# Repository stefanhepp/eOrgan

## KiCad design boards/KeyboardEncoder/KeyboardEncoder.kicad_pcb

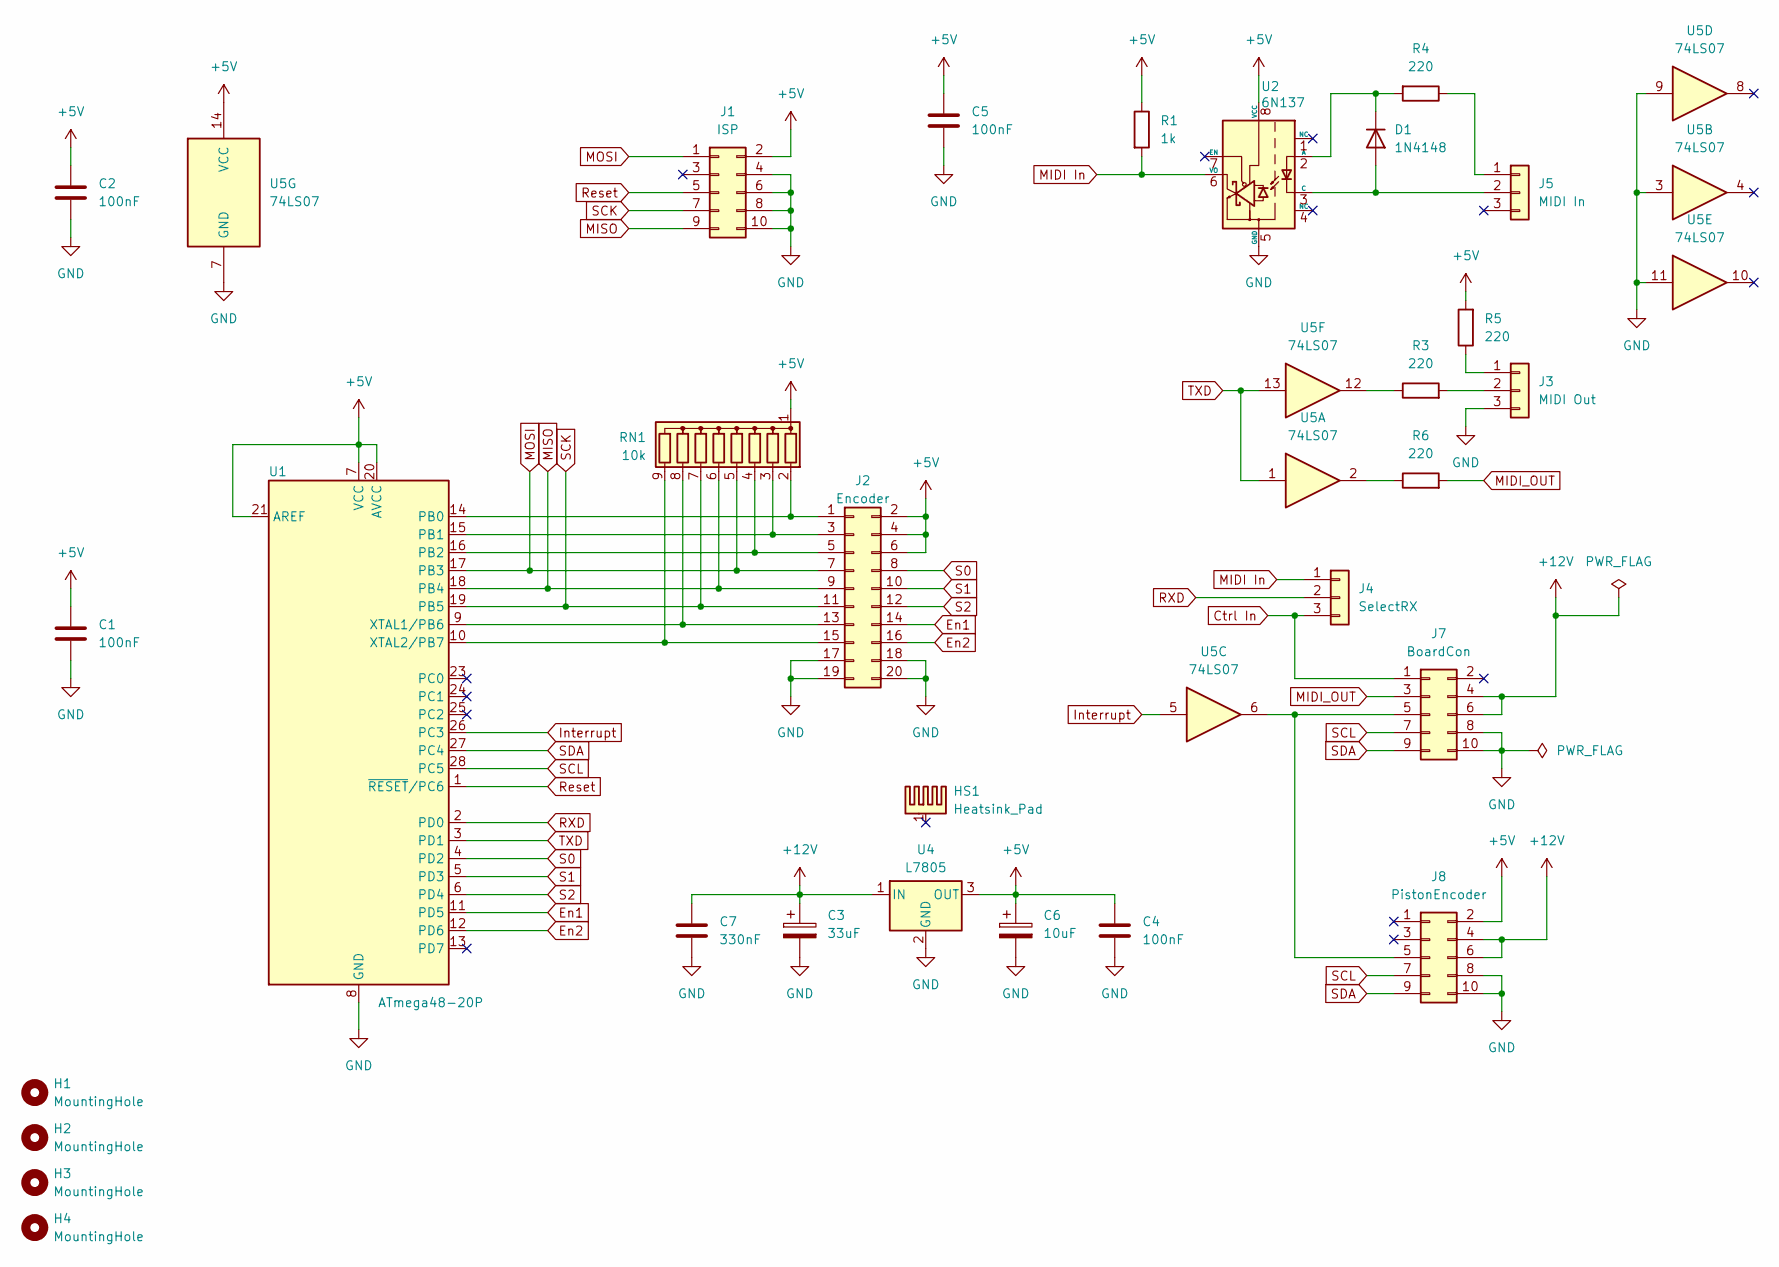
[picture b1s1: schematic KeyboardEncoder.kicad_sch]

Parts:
C1, C2, C4, C5: 100nF; C_Disc_D4.3mm_W1.9mm_P5.00mm
C3: 33uF; CP_Radial_D7.5mm_P2.50mm
C6: 10uF; CP_Radial_D5.0mm_P2.00mm
C7: 330nF; C_Disc_D4.3mm_W1.9mm_P5.00mm
D1: 1N4148; D_DO-35_SOD27_P7.62mm_Horizontal
H1, H2, H3, H4: MountingHole; MountingHole_3.2mm_M3
HS1: Heatsink_Pad; Heatsink_Aavid_TO-220_H12.7mm
J1: ISP; IDC-Header_2x05_P2.54mm_Horizontal
J2: Encoder; IDC-Header_2x10_P2.54mm_Horizontal
J3: MIDI Out; PinHeader_1x03_P2.54mm_Vertical
J4: SelectRX; PinHeader_1x03_P2.54mm_Vertical
J5: MIDI In; PinHeader_1x03_P2.54mm_Vertical
J7: BoardCon; IDC-Header_2x05_P2.54mm_Horizontal
J8: PistonEncoder; IDC-Header_2x05_P2.54mm_Vertical
R1: 1k; R_Axial_DIN0207_L6.3mm_D2.5mm_P2.54mm_Vertical
R3, R4, R5, R6: 220; R_Axial_DIN0207_L6.3mm_D2.5mm_P10.16mm_Horizontal
RN1: 10k; R_Array_SIP9
U1: ATmega48-20P; DIP-28_W7.62mm
U2: 6N137; DIP-8_W7.62mm
U4: L7805; TO-220-3_Vertical
U5: 74LS07; DIP-14_W7.62mm

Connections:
+5V: C1.1, C2.1, C4.1, C5.1, C6.1, J1.2, J2.2, J2.4, J2.6, J8.2, R1.1, R5.2, RN1.1 (common), U1.7 (VCC), U1.20 (AVCC), U1.21 (AREF), U2.8 (VCC), U4.3 (OUT), U5.14 (VCC)
+12V: C3.1, C7.1, J7.4, J7.6, J8.4, J8.6, U4.1 (IN)
Ctrl In: J4.3, J7.1
En1: J2.14, U1.11 (PD5)
En2: J2.16, U1.12 (PD6)
GND: C1.2, C2.2, C3.2, C4.2, C5.2, C6.2, C7.2, J1.4, J1.6, J1.8, J1.10, J2.17, J2.18, J2.19, J2.20, J3.3, J7.8, J7.10, J8.8, J8.10, U1.8 (GND), U1.22 (GND), U2.5 (GND), U4.2 (GND), U5.3, U5.7 (GND), U5.9, U5.11
Interrupt: U1.26 (PC3), U5.5
MIDI In: J4.1, R1.2, U2.6 (VO)
MIDI_OUT: J7.3, R6.2
MISO: J1.9, J2.9, RN1.6 (R5), U1.18 (PB4)
MOSI: J1.1, J2.7, RN1.5 (R4), U1.17 (PB3)
unnamed: D1.2 (A), J5.2, U2.3 (C)
unnamed: D1.1 (K), R4.2, U2.2 (A)
unnamed: J2.1, RN1.2 (R1), U1.14 (PB0)
unnamed: J2.3, RN1.3 (R2), U1.15 (PB1)
unnamed: J2.5, RN1.4 (R3), U1.16 (PB2)
unnamed: J2.13, RN1.8 (R7), U1.9 (XTAL1/PB6)
unnamed: J2.15, RN1.9 (R8), U1.10 (XTAL2/PB7)
unnamed: J3.1, R5.1
unnamed: J3.2, R3.2
unnamed: J5.1, R4.1
unnamed: J7.5, J8.5, U5.6
unnamed: R3.1, U5.12
unnamed: R6.1, U5.2
RXD: J4.2, U1.2 (PD0)
Reset: J1.5, U1.1 (~RESET/PC6)
S0: J2.8, U1.4 (PD2)
S1: J2.10, U1.5 (PD3)
S2: J2.12, U1.6 (PD4)
SCK: J1.7, J2.11, RN1.7 (R6), U1.19 (PB5)
SCL: J7.7, J8.7, U1.28 (PC5)
SDA: J7.9, J8.9, U1.27 (PC4)
TXD: U1.3 (PD1), U5.1, U5.13

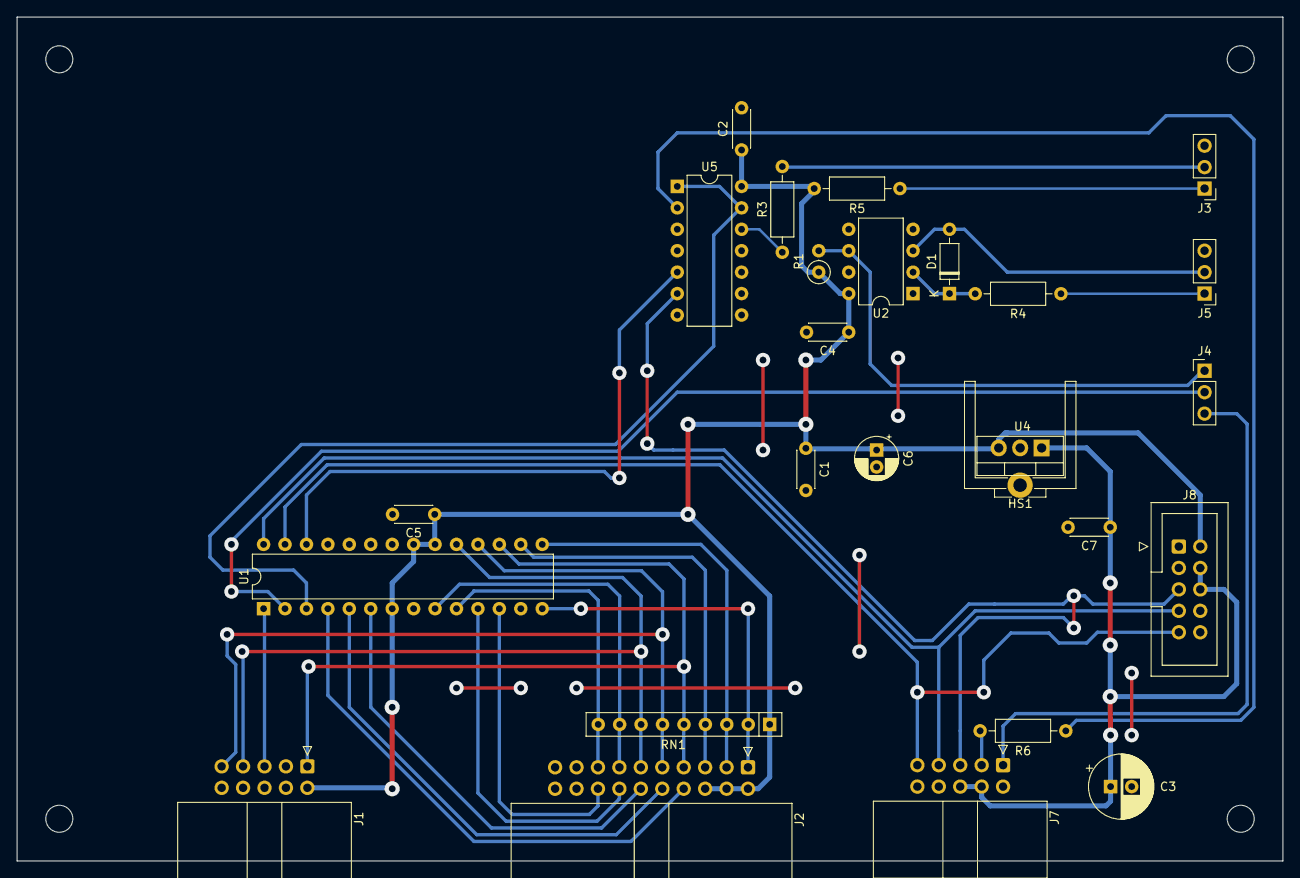
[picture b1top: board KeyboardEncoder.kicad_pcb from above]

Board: 2 copper layers, 150.0 x 100.0 mm, 30 parts (0 on the bottom side), 33 nets.

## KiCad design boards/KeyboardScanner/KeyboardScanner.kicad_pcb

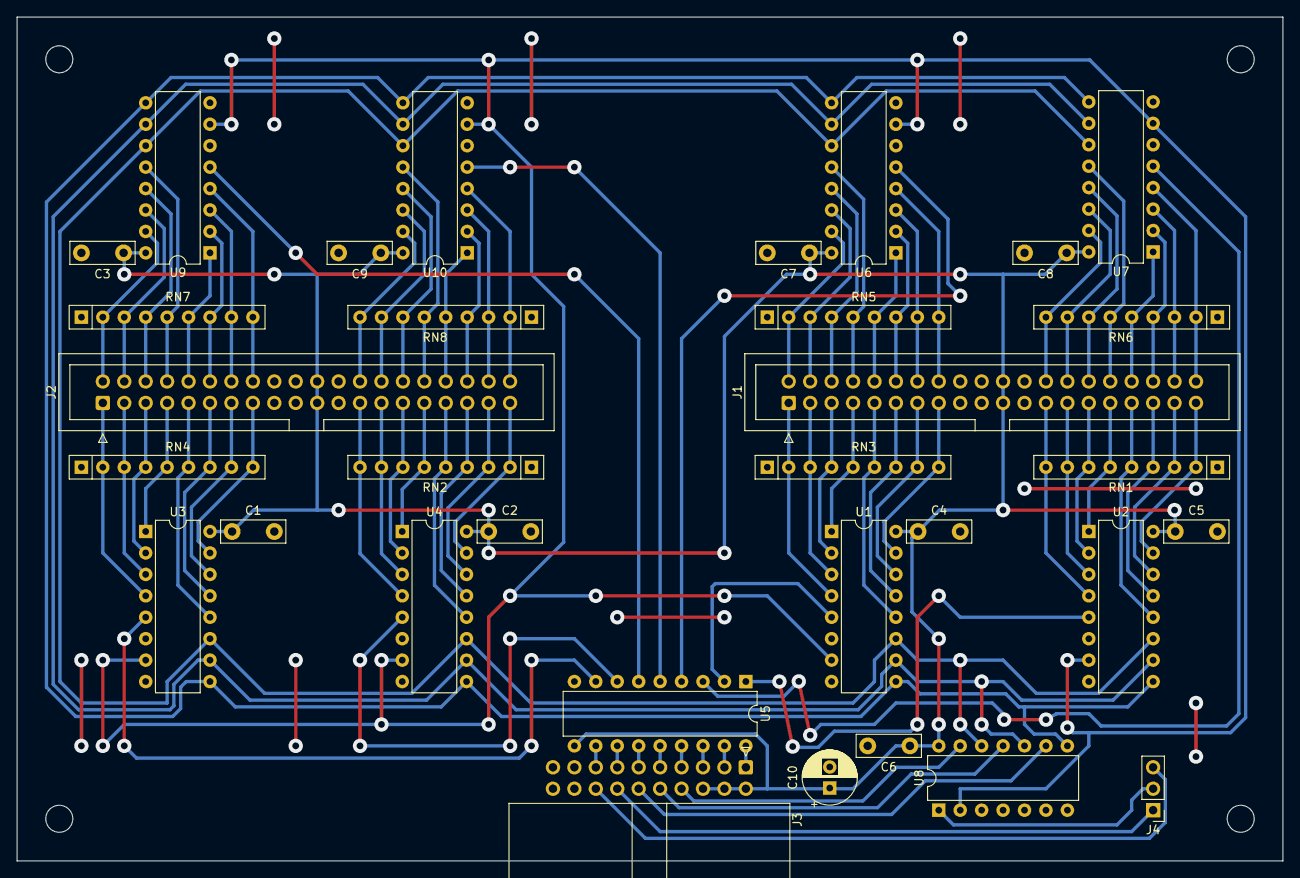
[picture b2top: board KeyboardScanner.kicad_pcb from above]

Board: 2 copper layers, 150.0 x 100.0 mm, 36 parts (0 on the bottom side), 92 nets.

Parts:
C1, C2, C3, C4, C5, C6, C7, C8, C9: 100nF; C_Disc_D7.5mm_W2.5mm_P5.00mm
C10: 47uF; CP_Radial_D6.3mm_P2.50mm
H1, H2, H3, H4: MountingHole; MountingHole_3.2mm_M3
J1, J2: Keyboard1; IDC-Header_2x20_P2.54mm_Vertical
J3: Encoder; IDC-Header_2x10_P2.54mm_Horizontal
J4: Select; PinHeader_1x03_P2.54mm_Vertical
RN1, RN2, RN3, RN4, RN5, RN6, RN7, RN8: 10k; R_Array_SIP9
U1, U2, U3, U4, U6, U7, U9, U10: 74LS151; DIP-16_W7.62mm
U5: ULN2803A; DIP-18_W7.62mm
U8: 4069; DIP-14_W7.62mm

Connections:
+5V: C1.1, C2.1, C3.1, C4.1, C5.1, C6.1, C7.1, C8.1, C9.1, C10.1, J1.21, J1.22, J2.21, J2.22, J3.2, J3.4, J3.6, U1.16 (VCC), U2.16 (VCC), U3.16 (VCC), U4.16 (VCC), U5.10 (COM), U6.16 (VCC), U7.16 (VCC), U8.14 (VDD), U9.16 (VCC), U10.16 (VCC)
En: U1.7 (~E), U2.7 (~E), U3.7 (~E), U4.7 (~E), U6.7 (~E), U7.7 (~E), U8.2, U9.7 (~E), U10.7 (~E)
GND: C1.2, C2.2, C3.2, C4.2, C5.2, C6.2, C7.2, C8.2, C9.2, C10.2, J3.17, J3.18, J3.19, J3.20, RN1.1 (common), RN2.1 (common), RN3.1 (common), RN4.1 (common), RN5.1 (common), RN6.1 (common), RN7.1 (common), RN8.1 (common), U1.8 (GND), U2.8 (GND), U3.8 (GND), U4.8 (GND), U5.9 (GND), U6.8 (GND), U7.8 (GND), U8.3, U8.5, U8.7 (VSS), U9.8 (GND), U10.8 (GND)
K01: J1.1, RN3.2 (R1), U1.4 (I0)
K02: J1.3, RN3.3 (R2), U1.3 (I1)
K03: J1.5, RN3.4 (R3), U1.2 (I2)
K04: J1.7, RN3.5 (R4), U1.1 (I3)
K05: J1.9, RN3.6 (R5), U1.12 (I7)
K06: J1.11, RN3.7 (R6), U1.13 (I6)
K07: J1.13, RN3.8 (R7), U1.14 (I5)
K08: J1.15, RN3.9 (R8), U1.15 (I4)
K09: J1.25, RN1.9 (R8), U2.4 (I0)
K10: J1.27, RN1.8 (R7), U2.3 (I1)
K11: J1.29, RN1.7 (R6), U2.2 (I2)
K12: J1.31, RN1.6 (R5), U2.1 (I3)
K13: J1.33, RN1.5 (R4), U2.12 (I7)
K14: J1.35, RN1.4 (R3), U2.13 (I6)
K15: J1.37, RN1.3 (R2), U2.14 (I5)
K16: J1.39, RN1.2 (R1), U2.15 (I4)
K17: J2.1, RN4.2 (R1), U3.4 (I0)
K18: J2.3, RN4.3 (R2), U3.3 (I1)
K19: J2.5, RN4.4 (R3), U3.2 (I2)
K20: J2.7, RN4.5 (R4), U3.1 (I3)
K21: J2.9, RN4.6 (R5), U3.12 (I7)
K22: J2.11, RN4.7 (R6), U3.13 (I6)
K23: J2.13, RN4.8 (R7), U3.14 (I5)
K24: J2.15, RN4.9 (R8), U3.15 (I4)
K25: J2.25, RN2.9 (R8), U4.4 (I0)
K26: J2.27, RN2.8 (R7), U4.3 (I1)
K27: J2.29, RN2.7 (R6), U4.2 (I2)
K28: J2.31, RN2.6 (R5), U4.1 (I3)
K29: J2.33, RN2.5 (R4), U4.12 (I7)
K30: J2.35, RN2.4 (R3), U4.13 (I6)
K31: J2.37, RN2.3 (R2), U4.14 (I5)
K32: J2.39, RN2.2 (R1), U4.15 (I4)
K33: J1.2, RN5.2 (R1), U6.15 (I4)
K34: J1.4, RN5.3 (R2), U6.14 (I5)
K35: J1.6, RN5.4 (R3), U6.13 (I6)
K36: J1.8, RN5.5 (R4), U6.12 (I7)
K37: J1.10, RN5.6 (R5), U6.1 (I3)
K38: J1.12, RN5.7 (R6), U6.2 (I2)
K39: J1.14, RN5.8 (R7), U6.3 (I1)
K40: J1.16, RN5.9 (R8), U6.4 (I0)
K41: J1.26, RN6.9 (R8), U7.15 (I4)
K42: J1.28, RN6.8 (R7), U7.14 (I5)
K43: J1.30, RN6.7 (R6), U7.13 (I6)
K44: J1.32, RN6.6 (R5), U7.12 (I7)
K45: J1.34, RN6.5 (R4), U7.1 (I3)
K46: J1.36, RN6.4 (R3), U7.2 (I2)
K47: J1.38, RN6.3 (R2), U7.3 (I1)
K48: J1.40, RN6.2 (R1), U7.4 (I0)
K49: J2.2, RN7.2 (R1), U9.15 (I4)
K50: J2.4, RN7.3 (R2), U9.14 (I5)
K51: J2.6, RN7.4 (R3), U9.13 (I6)
K52: J2.8, RN7.5 (R4), U9.12 (I7)
K53: J2.10, RN7.6 (R5), U9.1 (I3)
K54: J2.12, RN7.7 (R6), U9.2 (I2)
K55: J2.14, RN7.8 (R7), U9.3 (I1)
K56: J2.16, RN7.9 (R8), U9.4 (I0)
K57: J2.26, RN8.9 (R8), U10.15 (I4)
K58: J2.28, RN8.8 (R7), U10.14 (I5)
K59: J2.30, RN8.7 (R6), U10.13 (I6)
K60: J2.32, RN8.6 (R5), U10.12 (I7)
K61: J2.34, RN8.5 (R4), U10.1 (I3)
K62: J2.36, RN8.4 (R3), U10.2 (I2)
K63: J2.38, RN8.3 (R2), U10.3 (I1)
K64: J2.40, RN8.2 (R1), U10.4 (I0)
unnamed: J3.1, U5.18 (O1)
unnamed: J3.3, U5.17 (O2)
unnamed: J3.5, U5.16 (O3)
unnamed: J3.7, U5.15 (O4)
unnamed: J3.8, U8.13
unnamed: J3.9, U5.14 (O5)
unnamed: J3.10, U8.11
unnamed: J3.11, U5.13 (O6)
unnamed: J3.12, U8.9
unnamed: J3.13, U5.12 (O7)
unnamed: J3.14, J4.1
unnamed: J3.15, U5.11 (O8)
unnamed: J3.16, J4.3
unnamed: J4.2, U8.1
O1: U1.5 (Z), U5.2 (I2)
O2: U2.5 (Z), U5.1 (I1)
O3: U3.5 (Z), U5.8 (I8)
O4: U4.5 (Z), U5.7 (I7)
O5: U5.4 (I4), U6.5 (Z)
O6: U5.3 (I3), U7.5 (Z)
O7: U5.6 (I6), U9.5 (Z)
O8: U5.5 (I5), U10.5 (Z)
S0: U1.11 (S0), U2.11 (S0), U3.11 (S0), U4.11 (S0), U6.11 (S0), U7.11 (S0), U8.12, U9.11 (S0), U10.11 (S0)
S1: U1.10 (S1), U2.10 (S1), U3.10 (S1), U4.10 (S1), U6.10 (S1), U7.10 (S1), U8.10, U9.10 (S1), U10.10 (S1)
S2: U1.9 (S2), U2.9 (S2), U3.9 (S2), U4.9 (S2), U6.9 (S2), U7.9 (S2), U8.8, U9.9 (S2), U10.9 (S2)

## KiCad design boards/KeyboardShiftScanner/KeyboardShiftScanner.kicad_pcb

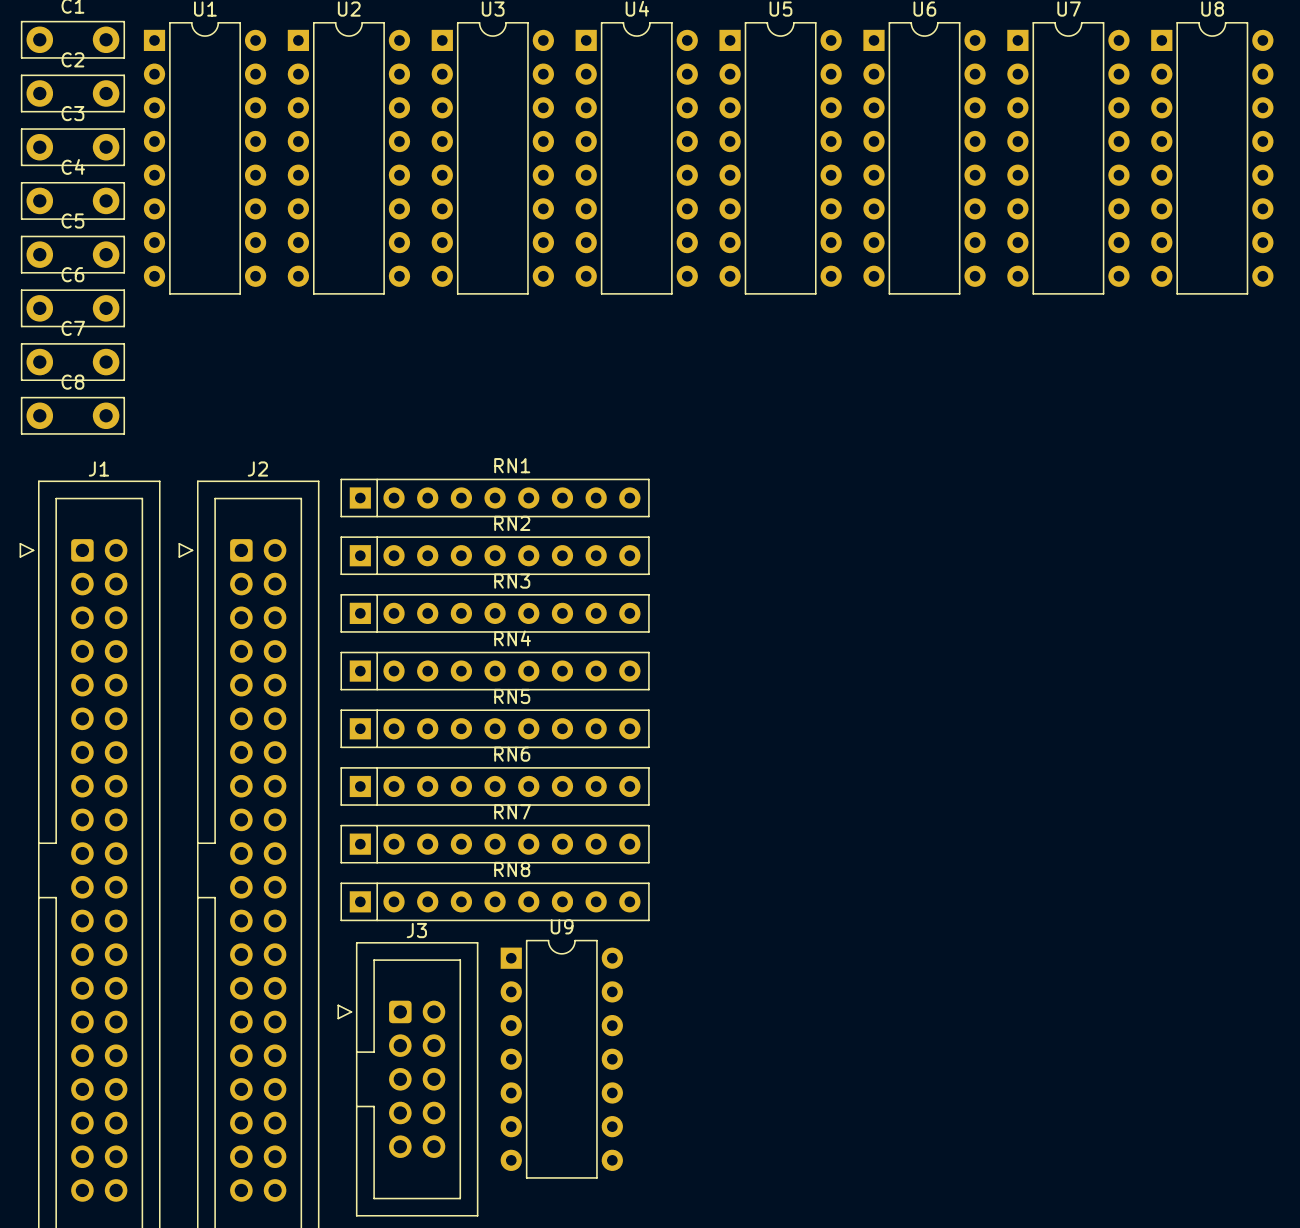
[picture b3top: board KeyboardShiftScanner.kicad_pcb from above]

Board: 2 copper layers, 28 parts (0 on the bottom side), 80 nets, no tracks yet.

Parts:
C1, C2, C3, C4, C5, C6, C7, C8: 100nF; C_Disc_D7.5mm_W2.5mm_P5.00mm
J1, J2: Keyboard1; IDC-Header_2x20_P2.54mm_Vertical
J3: Encoder; IDC-Header_2x05_P2.54mm_Vertical
RN1, RN2, RN3, RN4, RN5, RN6, RN7, RN8: 10k; R_Array_SIP9
U1, U2, U3, U4, U5, U6, U7, U8: 4014; DIP-16_W7.62mm
U9: 4069; DIP-14_W7.62mm

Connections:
+5V: C1.1, C2.1, C3.1, C4.1, C5.1, C6.1, C7.1, C8.1, J1.21, J2.21, J3.2, J3.4, U1.16 (Vdd), U2.16 (Vdd), U3.16 (Vdd), U4.16 (Vdd), U5.16 (Vdd), U6.16 (Vdd), U7.16 (Vdd), U8.16 (Vdd), U9.7 (VSS)
CP: U1.10 (CP), U2.10 (CP), U3.10 (CP), U4.10 (CP), U5.10 (CP), U6.10 (CP), U7.10 (CP), U8.10 (CP), U9.4
GND: C1.2, C2.2, C3.2, C4.2, C5.2, C6.2, C7.2, C8.2, J3.8, J3.10, RN1.1 (common), RN2.1 (common), RN3.1 (common), RN4.1 (common), RN5.1 (common), RN6.1 (common), RN7.1 (common), RN8.1 (common), U1.8 (Vss), U1.11 (DS), U2.8 (Vss), U3.8 (Vss), U3.11 (DS), U4.8 (Vss), U5.8 (Vss), U5.11 (DS), U6.8 (Vss), U7.8 (Vss), U7.11 (DS), U8.8 (Vss), U9.5, U9.13, U9.14 (VDD)
K01: J1.1, RN3.9 (R8), U1.7 (P0)
K02: J1.3, RN3.8 (R7), U1.6 (P1)
K03: J1.5, RN3.7 (R6), U1.5 (P2)
K04: J1.7, RN3.6 (R5), U1.4 (P3)
K05: J1.9, RN3.5 (R4), U1.13 (P4)
K06: J1.11, RN3.4 (R3), U1.14 (P5)
K07: J1.13, RN3.3 (R2), U1.15 (P6)
K08: J1.15, RN3.2 (R1), U1.1 (P7)
K09: J1.25, RN1.9 (R8), U2.7 (P0)
K10: J1.27, RN1.8 (R7), U2.6 (P1)
K11: J1.29, RN1.7 (R6), U2.5 (P2)
K12: J1.31, RN1.6 (R5), U2.4 (P3)
K13: J1.33, RN1.5 (R4), U2.13 (P4)
K14: J1.35, RN1.4 (R3), U2.14 (P5)
K15: J1.37, RN1.3 (R2), U2.15 (P6)
K16: J1.39, RN1.2 (R1), U2.1 (P7)
K17: J2.1, RN4.9 (R8), U3.7 (P0)
K18: J2.3, RN4.8 (R7), U3.6 (P1)
K19: J2.5, RN4.7 (R6), U3.5 (P2)
K20: J2.7, RN4.6 (R5), U3.4 (P3)
K21: J2.9, RN4.5 (R4), U3.13 (P4)
K22: J2.11, RN4.4 (R3), U3.14 (P5)
K23: J2.13, RN4.3 (R2), U3.15 (P6)
K24: J2.15, RN4.2 (R1), U3.1 (P7)
K25: J2.25, RN2.9 (R8), U4.7 (P0)
K26: J2.27, RN2.8 (R7), U4.6 (P1)
K27: J2.29, RN2.7 (R6), U4.5 (P2)
K28: J2.31, RN2.6 (R5), U4.4 (P3)
K29: J2.33, RN2.5 (R4), U4.13 (P4)
K30: J2.35, RN2.4 (R3), U4.14 (P5)
K31: J2.37, RN2.3 (R2), U4.15 (P6)
K32: J2.39, RN2.2 (R1), U4.1 (P7)
K33: J1.2, RN5.2 (R1), U5.7 (P0)
K34: J1.4, RN5.3 (R2), U5.6 (P1)
K35: J1.6, RN5.4 (R3), U5.5 (P2)
K36: J1.8, RN5.5 (R4), U5.4 (P3)
K37: J1.10, RN5.6 (R5), U5.13 (P4)
K38: J1.12, RN5.7 (R6), U5.14 (P5)
K39: J1.14, RN5.8 (R7), U5.15 (P6)
K40: J1.16, RN5.9 (R8), U5.1 (P7)
K41: J1.26, RN6.9 (R8), U6.7 (P0)
K42: J1.28, RN6.8 (R7), U6.6 (P1)
K43: J1.30, RN6.7 (R6), U6.5 (P2)
K44: J1.32, RN6.6 (R5), U6.4 (P3)
K45: J1.34, RN6.5 (R4), U6.13 (P4)
K46: J1.36, RN6.4 (R3), U6.14 (P5)
K47: J1.38, RN6.3 (R2), U6.15 (P6)
K48: J1.40, RN6.2 (R1), U6.1 (P7)
K49: J2.2, RN7.2 (R1), U7.7 (P0)
K50: J2.4, RN7.3 (R2), U7.6 (P1)
K51: J2.6, RN7.4 (R3), U7.5 (P2)
K52: J2.8, RN7.5 (R4), U7.4 (P3)
K53: J2.10, RN7.6 (R5), U7.13 (P4)
K54: J2.12, RN7.7 (R6), U7.14 (P5)
K55: J2.14, RN7.8 (R7), U7.15 (P6)
K56: J2.16, RN7.9 (R8), U7.1 (P7)
K57: J2.26, RN8.9 (R8), U8.7 (P0)
K58: J2.28, RN8.8 (R7), U8.6 (P1)
K59: J2.30, RN8.7 (R6), U8.5 (P2)
K60: J2.32, RN8.6 (R5), U8.4 (P3)
K61: J2.34, RN8.5 (R4), U8.13 (P4)
K62: J2.36, RN8.4 (R3), U8.14 (P5)
K63: J2.38, RN8.3 (R2), U8.15 (P6)
K64: J2.40, RN8.2 (R1), U8.1 (P7)
unnamed: J3.1, U9.1
unnamed: J3.6, U9.11
unnamed: U1.3 (Q7), U2.11 (DS)
unnamed: U3.3 (Q7), U4.11 (DS)
unnamed: U5.3 (Q7), U6.11 (DS)
unnamed: U7.3 (Q7), U8.11 (DS)
unnamed: U9.2, U9.3
unnamed: U9.9, U9.10
PL: U1.9 (PL), U2.9 (PL), U3.9 (PL), U4.9 (PL), U5.9 (PL), U6.9 (PL), U7.9 (PL), U8.9 (PL), U9.8
S1: J3.3, U2.3 (Q7)
S2: J3.5, U4.3 (Q7)
S3: J3.7, U6.3 (Q7)
S4: J3.9, U8.3 (Q7)

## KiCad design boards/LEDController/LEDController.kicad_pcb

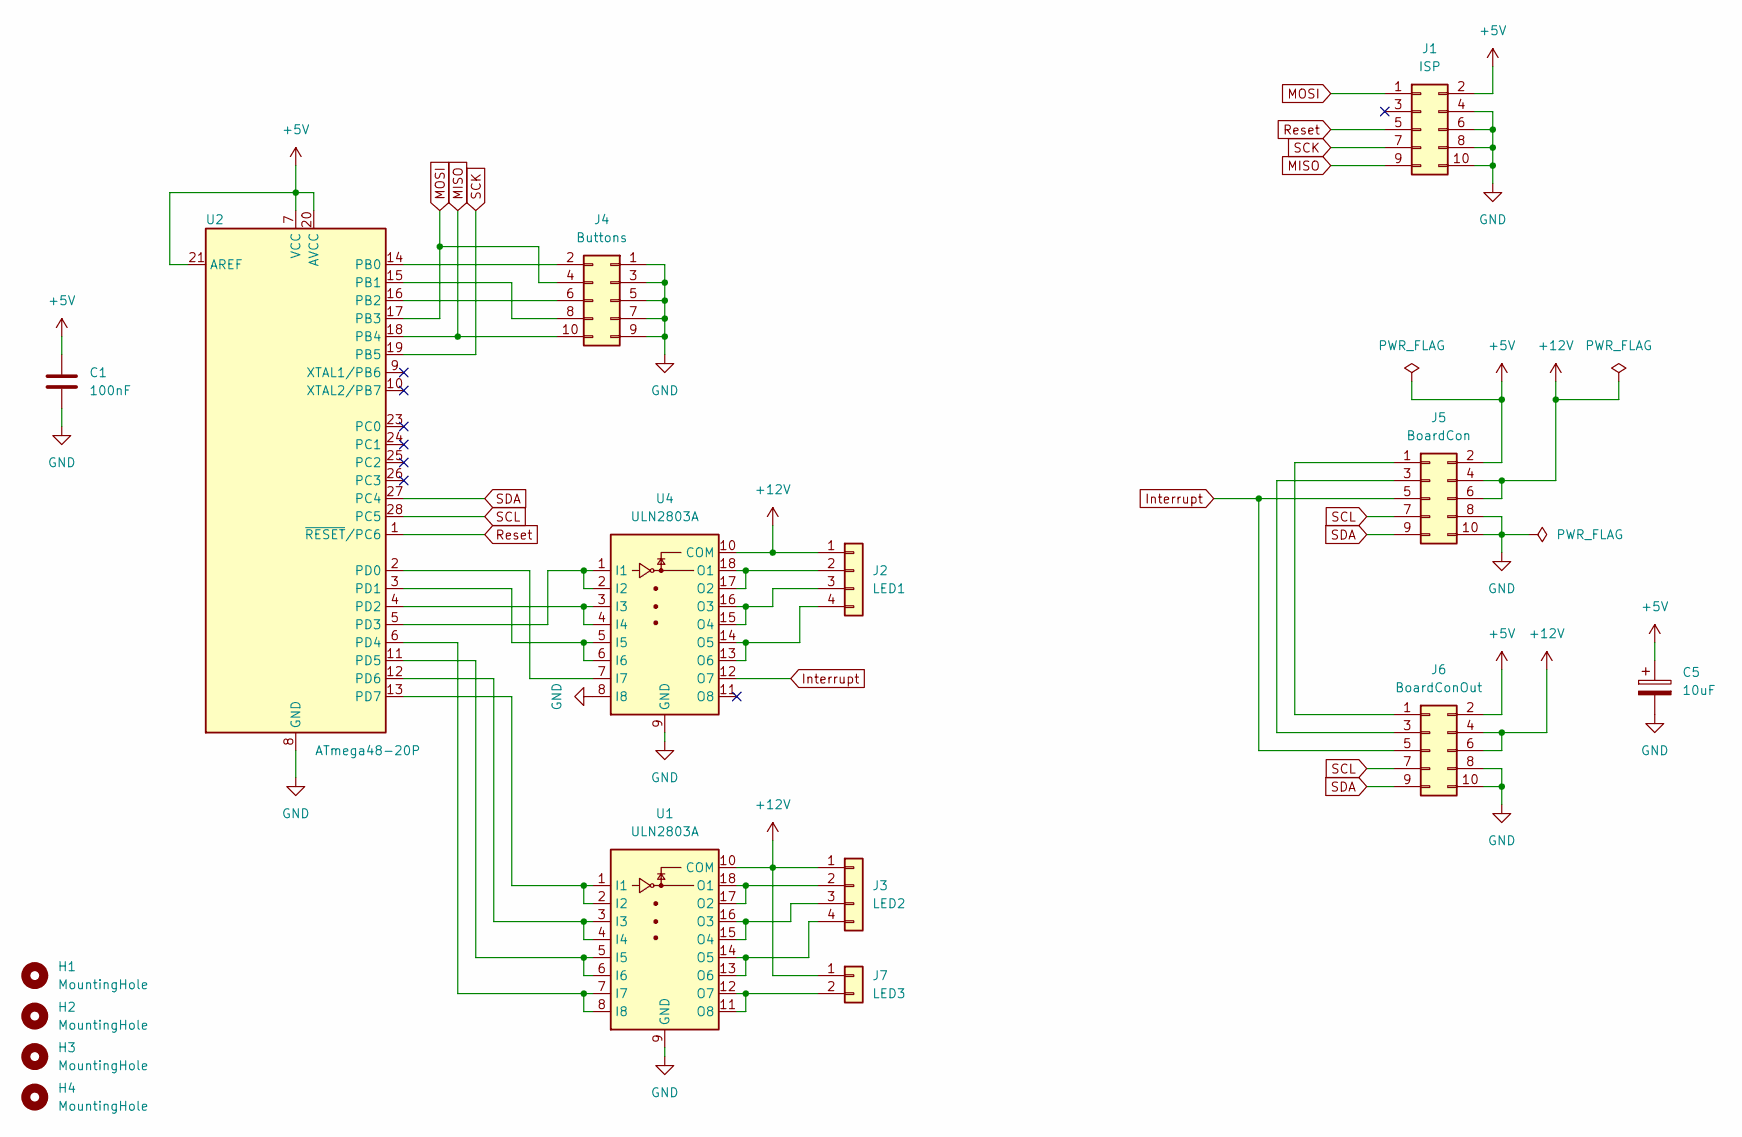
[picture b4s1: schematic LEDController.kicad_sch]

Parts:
C1: 100nF; C_Disc_D4.3mm_W1.9mm_P5.00mm
C5: 10uF; CP_Radial_D6.3mm_P2.50mm
H1, H2, H3, H4: MountingHole; MountingHole_3mm
J1: ISP; IDC-Header_2x05_P2.54mm_Vertical
J2: LED1; PinHeader_1x04_P2.54mm_Vertical
J3: LED2; PinHeader_1x04_P2.54mm_Vertical
J4: Buttons; PinHeader_2x05_P2.54mm_Vertical
J5: BoardCon; IDC-Header_2x05_P2.54mm_Vertical
J6: BoardConOut; IDC-Header_2x05_P2.54mm_Vertical
J7: LED3; PinHeader_1x02_P2.54mm_Vertical
U1, U4: ULN2803A; DIP-18_W7.62mm
U2: ATmega48-20P; DIP-28_W7.62mm_Socket

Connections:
+5V: C1.1, C5.1, J1.2, J5.2, J6.2, U2.7 (VCC), U2.20 (AVCC), U2.21 (AREF)
+12V: J2.1, J3.1, J5.4, J5.6, J6.4, J6.6, J7.1, U1.10 (COM), U4.10 (COM)
GND: C1.2, C5.2, J1.4, J1.6, J1.8, J1.10, J4.1, J4.3, J4.5, J4.7, J4.9, J5.8, J5.10, J6.8, J6.10, U1.9 (GND), U2.8 (GND), U2.22 (GND), U4.8 (I8), U4.9 (GND)
Interrupt: J5.5, J6.5, U4.12 (O7)
MISO: J1.9, J4.10, U2.18 (PB4)
MOSI: J1.1, J4.4, U2.17 (PB3)
unnamed: J2.2, U4.17 (O2), U4.18 (O1)
unnamed: J2.3, U4.15 (O4), U4.16 (O3)
unnamed: J2.4, U4.13 (O6), U4.14 (O5)
unnamed: J3.2, U1.17 (O2), U1.18 (O1)
unnamed: J3.3, U1.15 (O4), U1.16 (O3)
unnamed: J3.4, U1.13 (O6), U1.14 (O5)
unnamed: J4.2, U2.14 (PB0)
unnamed: J4.6, U2.16 (PB2)
unnamed: J4.8, U2.15 (PB1)
unnamed: J5.1, J6.1
unnamed: J5.3, J6.3
unnamed: J7.2, U1.11 (O8), U1.12 (O7)
unnamed: U1.1 (I1), U1.2 (I2), U2.13 (PD7)
unnamed: U1.3 (I3), U1.4 (I4), U2.12 (PD6)
unnamed: U1.5 (I5), U1.6 (I6), U2.11 (PD5)
unnamed: U1.7 (I7), U1.8 (I8), U2.6 (PD4)
unnamed: U2.2 (PD0), U4.7 (I7)
unnamed: U2.3 (PD1), U4.5 (I5), U4.6 (I6)
unnamed: U2.4 (PD2), U4.3 (I3), U4.4 (I4)
unnamed: U2.5 (PD3), U4.1 (I1), U4.2 (I2)
Reset: J1.5, U2.1 (~RESET/PC6)
SCK: J1.7, U2.19 (PB5)
SCL: J5.7, J6.7, U2.28 (PC5)
SDA: J5.9, J6.9, U2.27 (PC4)

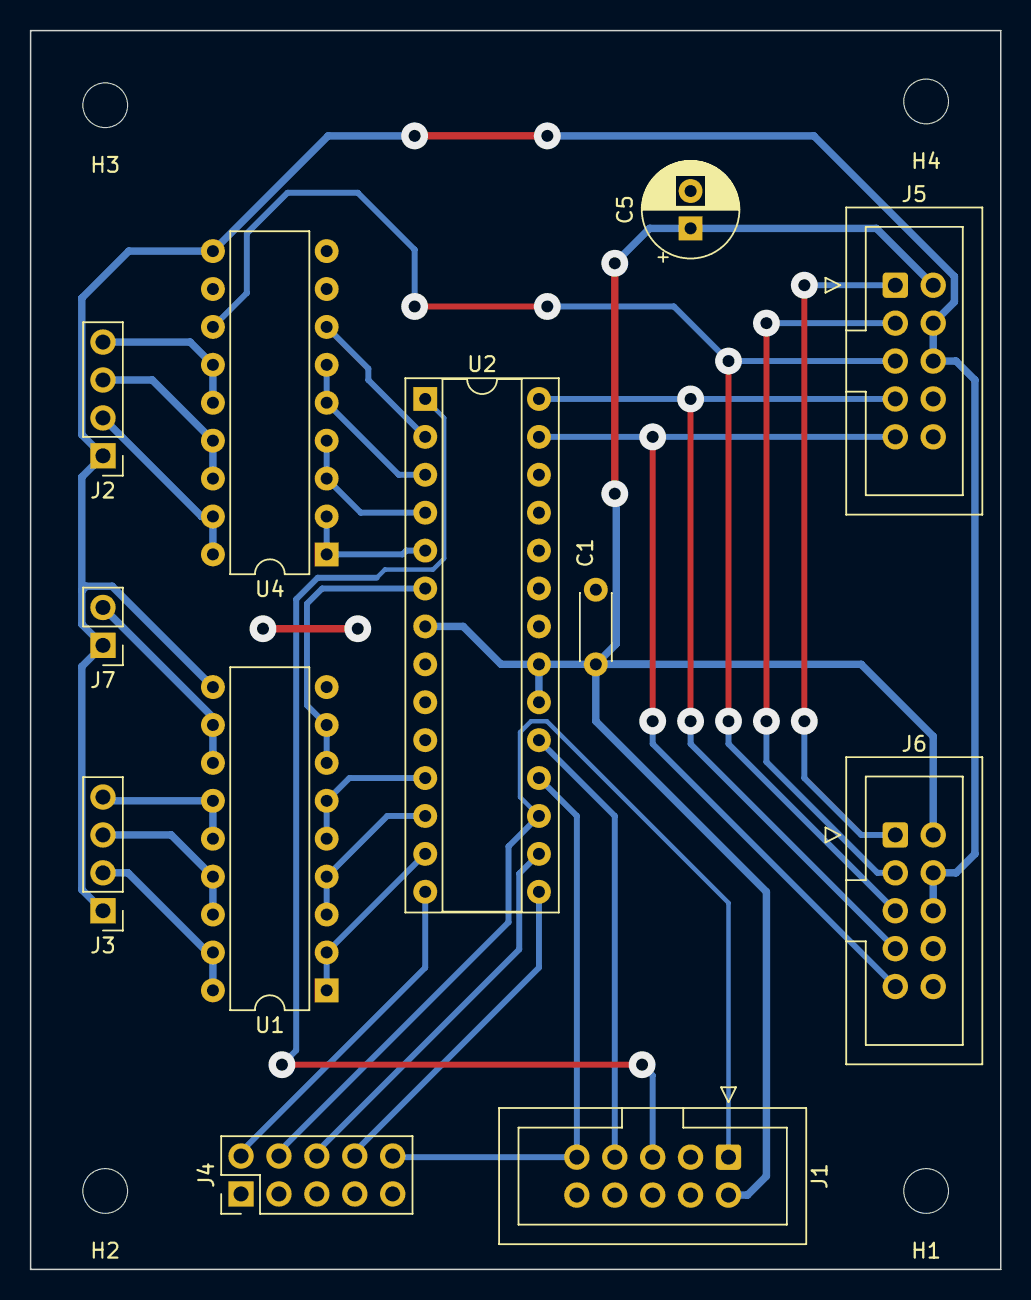
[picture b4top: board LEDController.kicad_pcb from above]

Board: 2 copper layers, 65.0 x 83.0 mm, 16 parts (0 on the bottom side), 30 nets.

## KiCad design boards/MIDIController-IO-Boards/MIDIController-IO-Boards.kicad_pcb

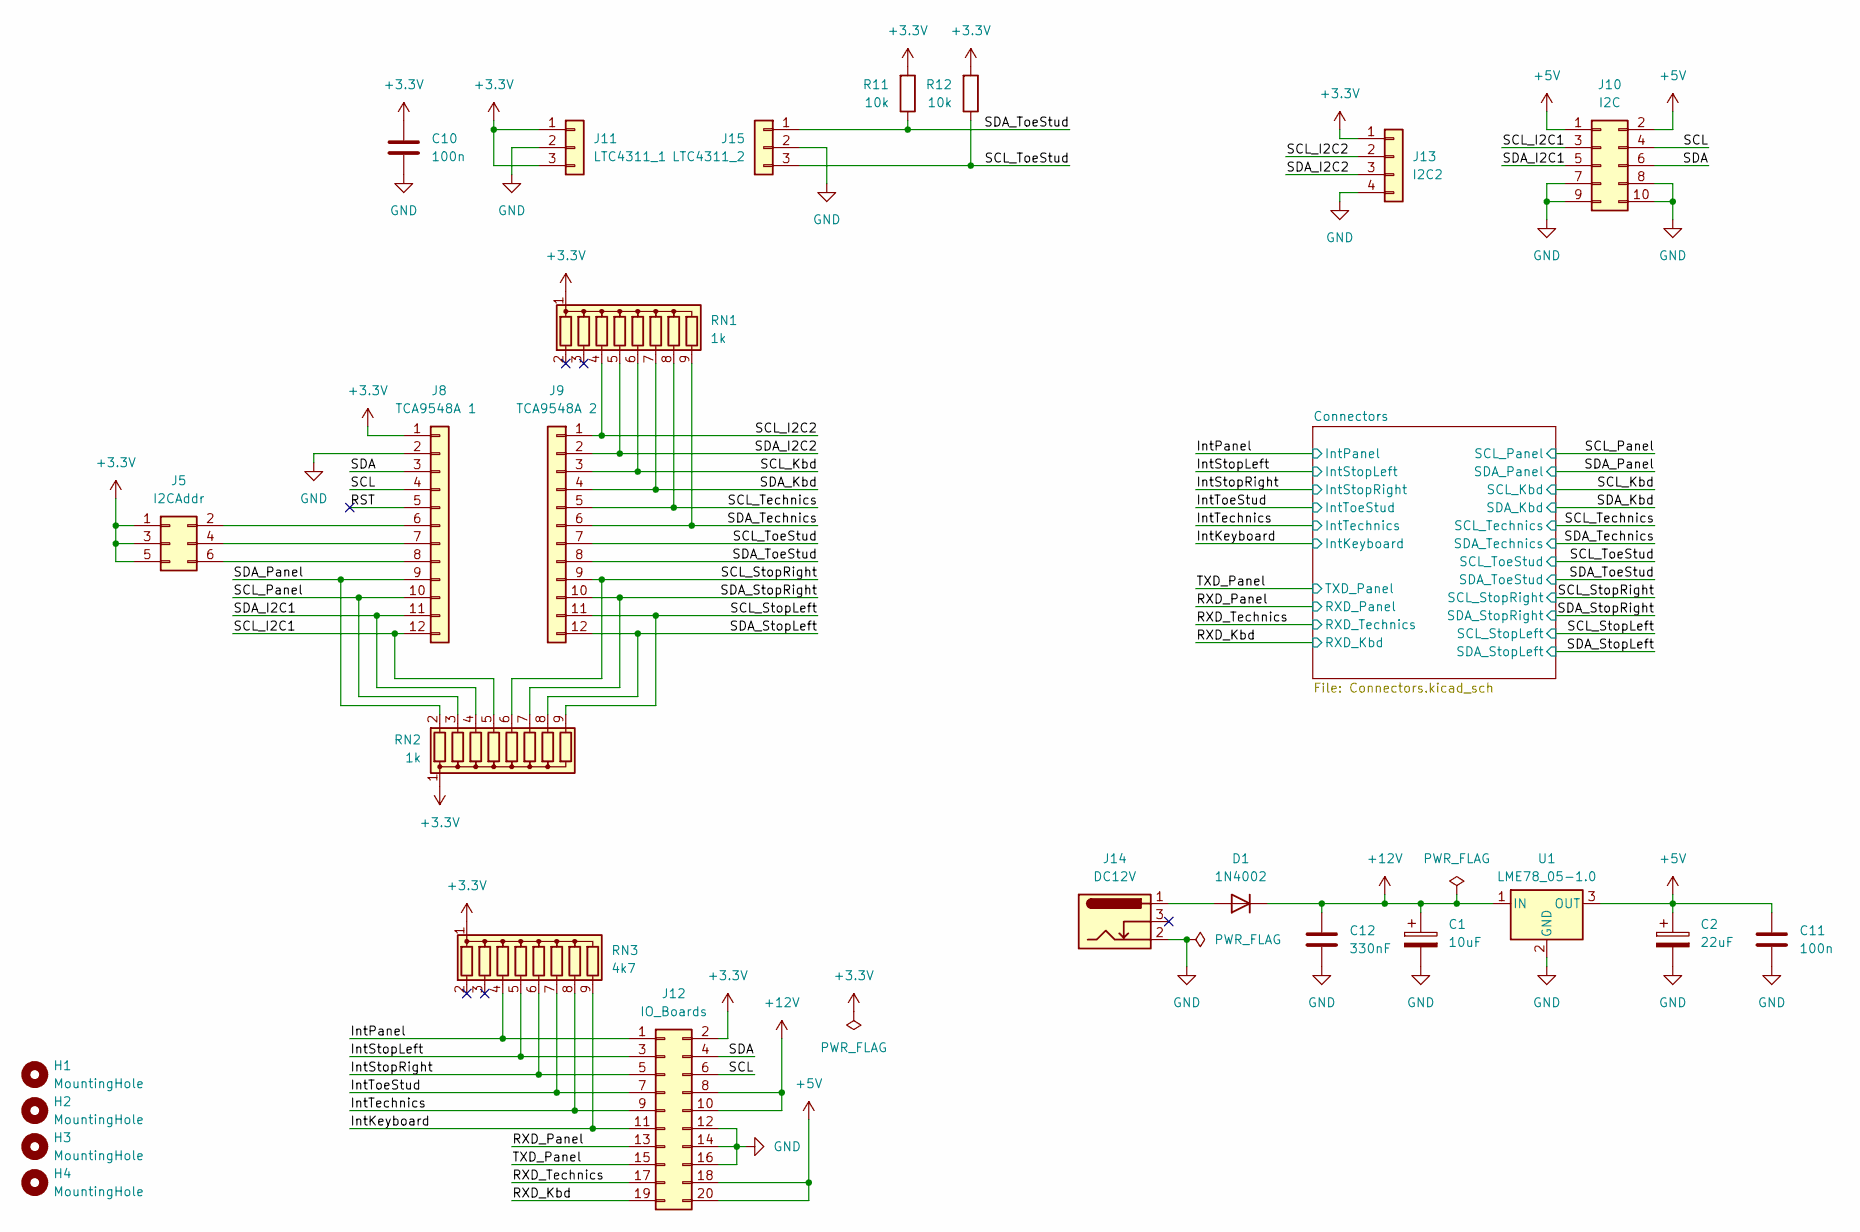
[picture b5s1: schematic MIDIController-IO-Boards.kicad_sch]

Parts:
C1: 10uF; CP_Radial_D5.0mm_P2.00mm
C2: 22uF; CP_Radial_D8.0mm_P2.50mm
C10, C11: 100n; C_Disc_D5.0mm_W2.5mm_P5.00mm
C12: 330nF; C_Disc_D5.0mm_W2.5mm_P5.00mm
D1: 1N4002; D_DO-41_SOD81_P10.16mm_Horizontal
H1, H2, H3, H4: MountingHole; MountingHole_3.2mm_M3
J5: I2CAddr; PinHeader_2x03_P2.54mm_Vertical
J8: TCA9548A 1; PinSocket_1x12_P2.54mm_Vertical
J9: TCA9548A 2; PinSocket_1x12_P2.54mm_Vertical
J10: I2C; IDC-Header_2x05_P2.54mm_Vertical
J11: LTC4311_1; PinSocket_1x03_P2.54mm_Vertical
J12: IO_Boards; IDC-Header_2x10_P2.54mm_Vertical
J13: I2C2; PinHeader_1x04_P2.54mm_Vertical
J14: DC12V; BarrelJack_Horizontal
J15: LTC4311_2; PinSocket_1x03_P2.54mm_Vertical
R11, R12: 10k; R_Axial_DIN0207_L6.3mm_D2.5mm_P10.16mm_Horizontal
RN1, RN2: 1k; R_Array_SIP9
RN3: 4k7; R_Array_SIP9
U1: LME78_05-1.0; Converter_DCDC_GAPTEC_LME78_05-1.0

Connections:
+3.3V: C10.1, J5.1, J5.3, J5.5, J8.1, J11.1, J11.3, J12.2, J13.1, R11.2, R12.2, RN1.1 (common), RN2.1 (common), RN3.1 (common); also elsewhere on the board
+5V: C2.1, C11.1, J10.1, J10.2, J12.18, J12.20, U1.3 (OUT); also elsewhere on the board
+12V: C1.1, C12.1, D1.1 (K), J12.8, J12.10, U1.1 (IN); also elsewhere on the board
/IntKeyboard: J12.11, RN3.9 (R8); also elsewhere on the board
/IntPanel: J12.1, RN3.4 (R3); also elsewhere on the board
/IntStopLeft: J12.3, RN3.5 (R4); also elsewhere on the board
/IntStopRight: J12.5, RN3.6 (R5); also elsewhere on the board
/IntTechnics: J12.9, RN3.8 (R7); also elsewhere on the board
/IntToeStud: J12.7, RN3.7 (R6); also elsewhere on the board
/RST: J8.5
/RXD_Kbd: J12.19; also elsewhere on the board
/RXD_Panel: J12.13; also elsewhere on the board
/RXD_Technics: J12.17; also elsewhere on the board
/SCL: J8.4, J10.4, J12.6
/SCL_I2C1: J8.12, J10.3, RN2.5 (R4)
/SCL_I2C2: J9.1, J13.2, RN1.4 (R3)
/SCL_Kbd: J9.3, RN1.6 (R5); also elsewhere on the board
/SCL_Panel: J8.10, RN2.3 (R2); also elsewhere on the board
/SCL_StopLeft: J9.11, RN2.9 (R8); also elsewhere on the board
/SCL_StopRight: J9.9, RN2.6 (R5); also elsewhere on the board
/SCL_Technics: J9.5, RN1.8 (R7); also elsewhere on the board
/SCL_ToeStud: J9.7, J15.3, R12.1; also elsewhere on the board
/SDA: J8.3, J10.6, J12.4
/SDA_I2C1: J8.11, J10.5, RN2.4 (R3)
/SDA_I2C2: J9.2, J13.3, RN1.5 (R4)
/SDA_Kbd: J9.4, RN1.7 (R6); also elsewhere on the board
/SDA_Panel: J8.9, RN2.2 (R1); also elsewhere on the board
/SDA_StopLeft: J9.12, RN2.8 (R7); also elsewhere on the board
/SDA_StopRight: J9.10, RN2.7 (R6); also elsewhere on the board
/SDA_Technics: J9.6, RN1.9 (R8); also elsewhere on the board
/SDA_ToeStud: J9.8, J15.1, R11.1; also elsewhere on the board
/TXD_Panel: J12.15; also elsewhere on the board
GND: C1.2, C2.2, C10.2, C11.2, C12.2, J8.2, J10.7, J10.8, J10.9, J10.10, J11.2, J12.12, J12.14, J12.16, J13.4, J14.2, J15.2, U1.2 (GND); also elsewhere on the board
unnamed: D1.2 (A), J14.1
unnamed: J5.2, J8.6
unnamed: J5.4, J8.7
unnamed: J5.6, J8.8
